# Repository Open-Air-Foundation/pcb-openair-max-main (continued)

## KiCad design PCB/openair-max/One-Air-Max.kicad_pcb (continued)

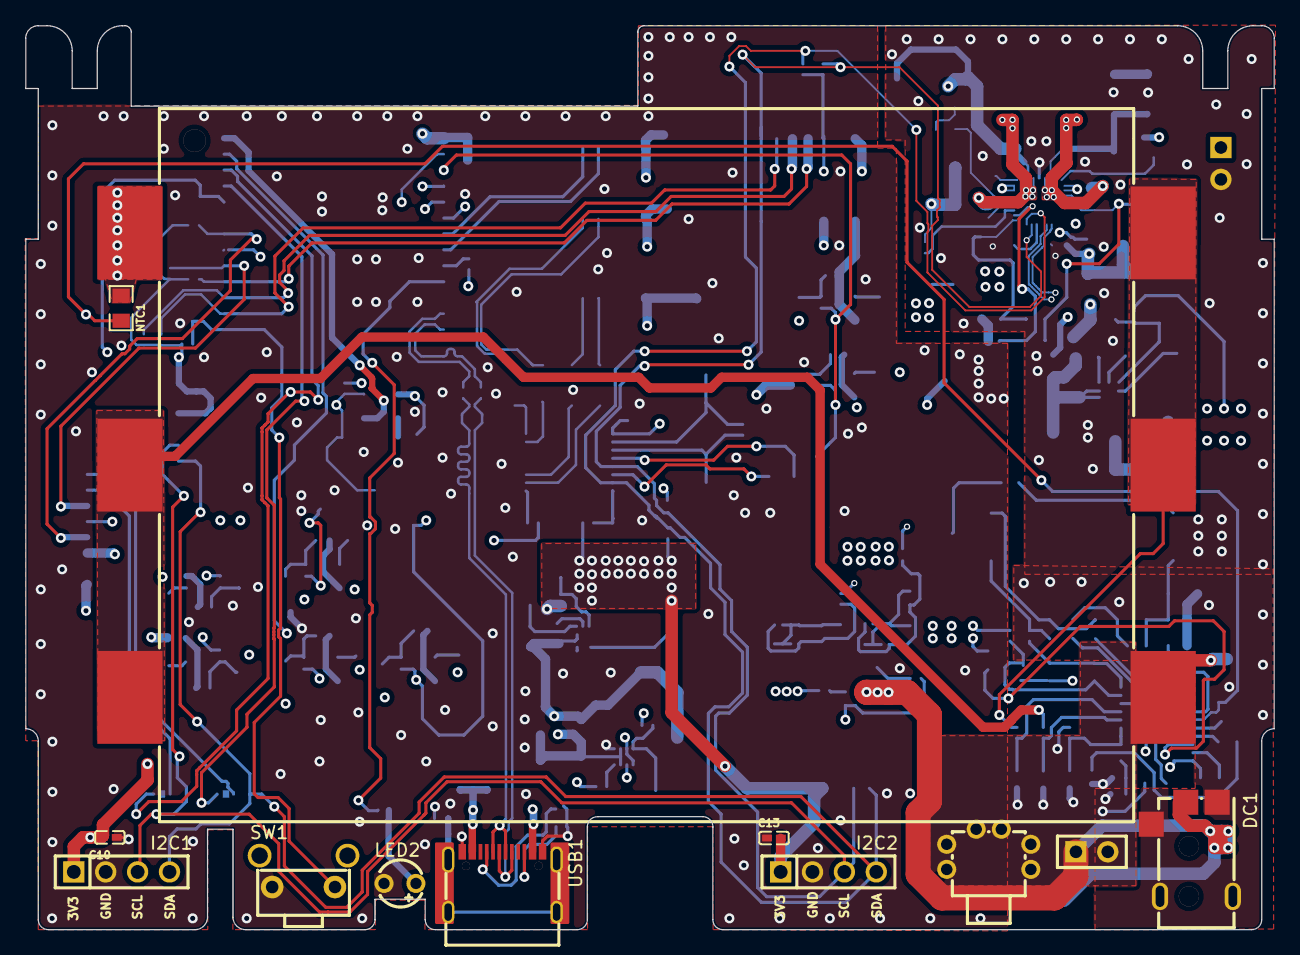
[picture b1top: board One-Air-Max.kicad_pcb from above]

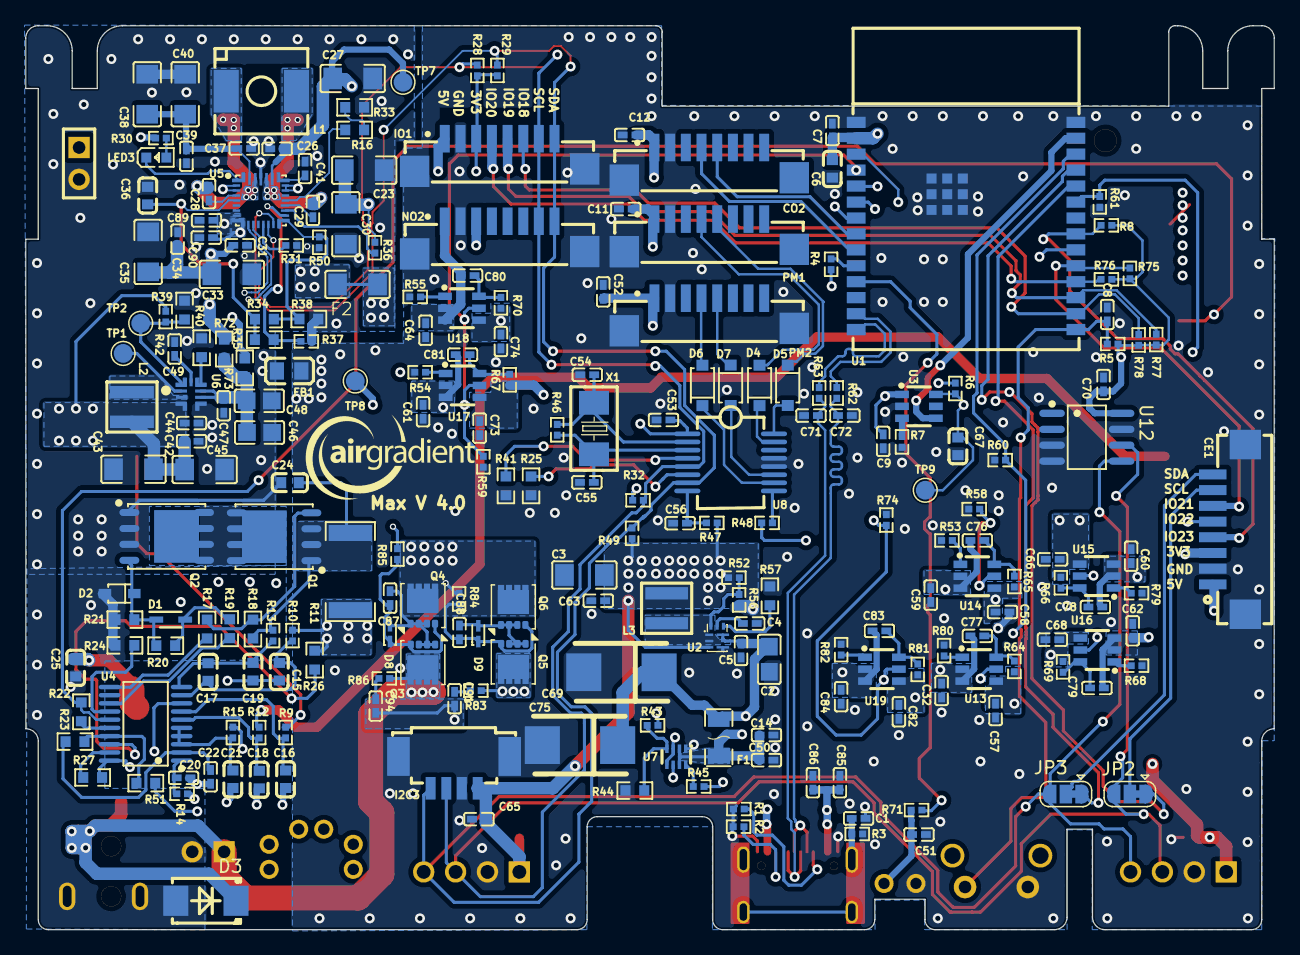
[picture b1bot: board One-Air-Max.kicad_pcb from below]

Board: 4 copper layers, 99.5 x 72.0 mm, 242 parts (230 on the bottom side), 138 nets.

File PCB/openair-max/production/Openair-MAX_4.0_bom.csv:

Designator,Footprint,Quantity,Value,LCSC Part #
"_6, _5, _4",212a6856-f275-4822-a761-75b07884269b,3,,
"_3, _2, ",bce4f5f5-1da5-494e-a908-01ed689de916,3,,
BAT1,BAT-SMD_BH-18650-B5BA016,1,BH-18650-B5BA016,C19184086
"C1, C10, C11, C12, C13, C50, C51, C52, C53, C65, C7, C70, C85, C9",C0402,14,0.1uF,C309458
"C14, C57, C58, C68, C74, C82, C86",C0402,7,22uF,C6119813
"C15, C16, C17, C18, C19, C21, C24, C25",C0603,8,0.1uF/50V,C14663
C2,C0805,1,10uF/25V,C3039694
"C20, C22",C0402,2,1uF/50V,C7500380
"C23, C27, C30",C1206,3,10uF/25V,C9807
"C26, C47",C0402,2,0.1uF/25V,C100072
"C28, C29",C0402,2,47nF/50V,C272875
C3,C1206,1,22uF/16V,C7472972
"C31, C34, C37, C39, C89, C90",C0402,6,0.1uF/50V,C77020
"C32, C59, C60, C61, C62, C64, C84",C0402,7,2.2uF,C385032
"C33, C35, C38, C40",C1206,4,10uF/50V,C13585
C36,C0603,1,4.7uF/16V,C22399629
"C4, C49",C0402,2,3.3nF,C541378
"C41, C87, C88",C0402,3,1nF/50V,C77018
"C42, C44, C5, C63",C0402,4,0.1uF,C1525
"C43, C45",C1206,2,10uF,C109464
"C46, C48",C0805,2,22uF/25V,C602037
"C54, C55",C0402,2,22pF_NM,C1555
C56,C0402,1,0.1nF,C106200
C6,C0603,1,22uF,C109447
"C66, C73, C76, C77, C78, C79, C80, C81, C83",C0402,9,1uF,C14445
C67,C0603,1,500pF,C1624
C69,CASE-D_7343,1,6TPE470MAZU,C79114
C8,C0402,1,10nF,C541371
"C91, C94",C0402,2,2.2uF/35V,C6119793
CE1,CONN-SMD_HC-1.25-8PWT,1,HC-1.25-8PWT,C2845385
"CO2, IO1, NO2, PM1, PM2",CONN-SMD_8P-P1.25_HC-1.25-8PLT,5,HC-1.25-8PLT,C2845394
D1,SOD2512X80N,1,BAS16J_135,
D2,SOD-323_L1.8-W1.3-LS2.5-RD,1,MMSZ5246BS-7-F,C151819
D3,SMB_L4.4-W3.6-LS5.3-RD,1,SMBJ24A_C908801,C908801
"D4, D5, D6, D7",SOD-123_L2.7-W1.6-LS3.7-FD,4,B5817W_C7420328,C7420328
"D8, D9",SOD-523_L1.2-W0.8-LS1.6-RD,2,BZT52C12T-7,C507911
DC1,DC-IN-SMD_DC-045A-13A,1,DC-045A-13A,C707277
F1,F1206,1,2A-16V,C2685749
FB1,L0805,1,PBY201209T-601Y-N,C108304
"I2C1, I2C2",HDR-TH_4P-P2.54-V-F,2,Conn_01x04,C2718488
I2C3,CONN-SMD_1.25-4PWB,1,1.25-4PWB,C2905011
L1,IND-SMD_L7.1-W6.5-P5.60,1,SPM6530T-1R0M120,C87572
L2,IND-SMD_L4.0-W4.0_XAL4030-332MEC,1,XGL4020-102MEC,C5357696
L3,IND-SMD_L4.0-W4.0_XGL4020,1,YSMC0420V-1R0M,C7433091
LED2,LED-TH_BD3.8-P2.54-FD_BLUE,1,XL-304UBC,C2895465
LED3,LED0603-RD_RED,1,FC-DA1608HRK-620D,C84263
NTC1,R0805,1,KNTC0805/10KF3950,C2892549
PWR_SW1,SW-TH_TK-6580A8-1,1,TK-6580A8-1,C528772
"Q1, Q2",PQFN-8_L5.8-W4.9-P1.27-LS6.0-BL,2,CSD18534Q5A,
"Q3, Q4, Q5, Q6",VSON-8_3.3x3.3mm_P0.65mm_NexFET,4,CSD17577Q3A,C201632
"R1, R2",R0402,2,5.1K,C105872
"R10, R13, R36",R0402,3,100,C606168
R11,R2512,1,10m / 1W,C705061
"R12, R14, R15, R9",R0402,4,1K,C851849
R16,R0603,1,10.5K,C137808
"R17, R19",R0603,2,5.1K,C105580
R18,R0603,1,10M,C114606
R20,R0603,1,1M,C105578
R21,R0603,1,3M,C126361
R22,R0603,1,10K,C98220
R24,R0603,1,470K,C114622
"R26, R27, R33, R41, R51, R72",R0603,6,0,C100044
"R28, R29, R30, R32, R4, R45, R49, R5, R50",R0402,9,10K,C60490
"R3, R31, R37, R6",R0402,4,100K,C60491
R34,R0603,1,5.23K,C185317
R35,R0603,1,255K,C295887
R38,R0603,1,30.1K,C137745
R39,R0402,1,200K,C606170
R40,R0603,1,27K,C114614
"R42, R57",R0603,2,7.15K,C861562
R43,R0402,1,16.9K,C163488
R44,R0603,1,5K,C862232
R46,R0402,1,1M,C327799
"R47, R58, R59, R60, R61, R64, R65, R66, R67, R69, R70, R74, R81",R0402,13,10K,C327797
R48,R0402,1,5.1K,C413002
R52,R0402,1,113k,C273332
"R53, R54, R55, R68, R79, R80, R82",R0402,7,1K,C106235
R56,R0402,1,24.9k,C226371
"R62, R63",R0402,2,22,C114765
R7,R0402,1,51K,C107229
R71,R0402,1,210,C2076880
"R83, R86",R0402,2,2,C514778
"R84, R85",R0402,2,294,C477682
SW1,KEY-TH_TS-1096-A1B2-D2,1,TS-1096-A1B2-D2,C492993
U1,WIRELM-SMD_ESP32-C6-WROOM-1,1,ESP32-C6-WROOM-1-N8,C5366877
U12,SOIC-8_L4.9-W3.9-P1.27-LS6.0-BL,1,AT24CM02-SSHD-B,C220680
"U13, U14, U15, U16, U17, U18, U19",SOT-23-6_L2.9-W1.6-P0.95-LS2.8-BR,7,TPS27081ADDCR,C128404
U2,VQFN-HR-9_L2.0-W1.5-P0.50-TL,1,TPS62902RPJR,C2870154
U3,SOT-23-6_L2.9-W1.6-P0.95-LS2.8-BR,1,TPL5010DDCR,C473912
U4,TSSOP-20_L6.5-W4.4-P0.65-LS6.4-BL,1,BQ7790512PWR,C555146
U5,QFN-29_L4.0-W4.0-P0.40-TL-BQ25792RQMR,1,BQ25798RQMR,C2876593
U6,VQFNHR-9_L2.2-W2.0_TPS62993QRYTRQ1,1,TPS62903QRYTRQ1_C20345985,C20345985
U7,SOT-583-8_L2.1-W1.2-P0.50-LS1.6-BL,1,TPS2117DRLR_C22399676,C22399676
U8,SSOP-16_L7.2-W5.3-P0.65-LS7.8-BL,1,WK2132-ISSG,C401039
USB1,USB-C-SMD_G-SWITCH_GT-USB-7010ASV,1,GT-USB-7010ASV,C2988369
X1,OSC-SMD_L5.0-W3.2,1,SMD-5032_2P 14.7456MHZ 20PF 20PPM,C362355
